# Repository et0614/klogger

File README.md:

# K-Logger v3 — 扉開閉記録装置

VL53L1X ToF距離センサで扉の開閉を検出し、内蔵フラッシュメモリに記録するデータロガー。
v2 からの主な変更点は以下のとおり（開発中）。

| 項目 | v2 | v3 |
|---|---|---|
| MCU | AVR32DB32 | AVR64DU32（ネイティブUSB） |
| PC通信 | CP2102N（USB-UART、要ドライバ） | USB-CDC（ドライバ不要） |
| 記録媒体 | microSD（FatFs、CSV） | W25Q128 16MB（バイナリ、PCツールでCSV化） |
| 電源 | 単3×1 | 単4×1、USB接続中はUSB給電（自動切替） |
| USB端子 | micro-B | Type-C |
| 電源スイッチ | スライド | なし（ボタン長押しでソフトOFF） |
| 基板CAD | Eagle | Fusion |

旧版（v2）は [v2/](v2/README.md) を参照。

## ディレクトリ構成

```
docs/
  index.html            ブラウザ版の操作ページ（GitHub Pages）
  images/               基板・3D外観画像
hardware/
  BOM.xlsx              設計用部品表（JLCPCB部品番号・リンク付き）
  datasheets/           主要部品データシート（ファイル名=参照記号）
  pcb/                  Fusion設計データ(klogger.f3z)、回路図PDF
  fab/                  JLCPCB入稿データ（ガーバー、JLCPCB_BOM.xlsx、JLCPCB_CPL.xlsx）
firmware/klogger.X/     MPLAB X プロジェクト（AVR64DU32, MCC Melody: klogger.mc3）。アプリは 0x0A00 以降に置く
firmware/bootloader/    USB ブートローダ（euboot）。USB でのファームウェア更新と、量産用の1ファイル化 (build_production_hex.py)
software/python/        PCツール: klogger_gui.py（GUI）、klogger.py（コマンド版・通信ライブラリ）、build_exe.bat（exe化）
v2/                     旧版 K-Logger v2 一式（凍結）
```

## バージョン

- 製品世代: K-Logger v3（v2 の後継）
- 基板: 3.1（シルク表記「Version 3.1」。3.0 からはシルクのみ変更、履歴は `hardware/fab/README.md`）。修正ごとに 3.2, 3.3 … と上げる。リポジトリには最新版のみを置き、過去の版は Git の履歴で参照する
- ファームウェア: 現在 3.2.0（`hello` 応答の `fw`。`firmware/klogger.X/version.h`）

## 使い方

### 動作モード
| 状態 | 入り方 | 動作 | LED |
|---|---|---|---|
| USB通信 | USBを挿す | PCツールからの操作を受け付ける（USB給電） | 1秒ごとに2回点滅 |
| 記録 | PCツールで記録開始 | 記録間隔ごとに距離を記録。USBを抜いても続ける | 消灯 |
| 待機（ソフトOFF） | USB無しで電池を入れる / 記録中にボタン5秒長押し / 電池切れ | 何もしない（省電力） | 消灯 |

- ボタンを押している間はLEDが点灯する（生存確認）。5秒長押しでリセット（記録中なら記録停止）。
- 記録中にUSBを挿すと記録を止めてUSB通信モードに戻る（データは保存される）。
- 記録開始時に既存データは消去される。先に読み出しておくこと。
- 電池を抜くと、まだフラッシュに書いていない最大128件（1秒間隔で約2分）が失われる。

### 消費電流・電池寿命
記録間隔1秒・測距条件 short / 20ms / ROI 4x4（既定、FW 3.1.1 から）で、記録中の電流は電池側で平均約0.6mA（実測、2026-11-20）。内訳は測距が約0.4mA、測距の合間（マイコンのスリープ、距離センサの待機、昇圧ICなど）が約0.2mA。タイミングバジェット 50ms では平均約1.2mA（測距が約0.9mA）で、Eneloop Pro（単4、約930mAh）を満充電して設置した実績は約16日だった（計算上は約1か月。電池電圧が下がるほど電池側の電流は増える）。
測距の分は記録間隔とタイミングバジェットにほぼ比例して減る。20ms は VL53L1X の最小値（short のみ）。50ms に比べて距離のばらつきは約2倍（近距離の標準偏差 約1mm → 約2mm）になり、遠い対象や強い外光では失敗が増えるが、扉の開閉の検出には影響しない。
待機中（記録停止後）も約0.2mA 流れる（昇圧IC の自己消費 17µA が主。3.3V を保つ限り減らせない）。満充電でも約半年で空になるので、使わないときは電池を抜く。
電流はクランプ電流計で、配線を5回巻いて測った（1回巻きでは1mA以下の精度が足りず、以前の「約0.5mA」は過小だった）。測距は1秒に1回の短いパルスなので、1秒ごとの読み取り値は、測距のパルスを含むかどうかで2つの値を行き来する（20ms で約0.2mA と約0.9mA）。平均はその読み取り値の平均で見る。

### ブラウザ版
パソコンの Chrome または Edge で https://et0614.github.io/klogger/ を開き、USB でつないで「接続」を押す（インストール不要）。記録の開始、CSV の保存（日ごとの v2 形式も可）、データの消去、ライブ表示、距離の校正、測距条件、自己診断ができる。ページは `docs/index.html`（Web Serial で USB の仮想 COM ポートを開く。GitHub Pages で main ブランチの `/docs` を公開する）。手元で試すときは `docs` で `python -m http.server` を実行して http://localhost:8000/ を開く（Web Serial は https か localhost でしか動かない）。

### PCツール（GUI）
[Releases](https://github.com/et0614/klogger/releases) から `KLogger.exe` をダウンロードしてダブルクリックで起動する（Pythonは不要）。
署名の無いexeのため、初回に Windows SmartScreen が出たら「詳細情報」→「実行」を選ぶ。
Pythonがある場合は `pip install pyserial` の後に `python klogger_gui.py` でも起動できる。画面表示は英語。

1. USBを挿して **Connect**（ポートは自動検出）。上部に機器情報（FW、機体ID、電池電圧、保存件数、記録期間、測距条件）が出る。
2. **Logging** タブ: 記録間隔を入れて **Start logging**。時刻はPCに合わせられ、既存データは消去される。開始すると機器はUSBから切り離されるので、そのまま抜いて設置する。
3. 回収したらUSBを挿して（記録は自動で止まる）**Connect**。**Data** タブの **Save as CSV** で保存する（v2互換の日別CSVも選べる）。
4. **Live view** タブ: 距離をリアルタイム表示（設置位置の確認用）。
5. **Settings** タブ: 測距モード（Short/Long）、タイミングバジェット、ROI、自己診断。

### 距離校正（GUIの Calibration タブ）
距離のオフセット（測定値のずれ）を補正する。結果は機器に保存される。

1. 先に **Settings** タブで、実際に使う測距条件にしておく（条件を変えたら校正し直す）。
2. グレーの反射板（反射率17%前後。写真用18%グレーカードなど、10cm角以上）をセンサ正面に垂直に置く。距離は140mmを推奨。直射日光は避ける。
3. 目標距離（Target distance）を入力し **Start live reading**。直近20回の平均・ばらつき（SD）・目標との差が表示される。
4. ランプが緑（全数が有効かつ SD 3mm 以下）になったら **Calibrate**。50回測定して オフセット = 目標距離 − 平均 を保存する。
5. 校正後は補正済みの距離が表示されるので、反射板を別の距離に動かしてずれを確認する。結果が悪ければ **Restore previous offset**（元に戻す）や **Reset offset to 0** を使う。

### PCツール（コマンド版 `software/python/klogger.py`）
`pip install pyserial` の後、USBを挿して実行する（COMポートは自動検出）。

```
python klogger.py info              機器情報・状態・電池電圧
python klogger.py start -i 1        時刻合わせ＋記録開始（記録間隔1秒）
python klogger.py read              保存データをCSVに保存（--daily フォルダ でv2互換の日別CSV）
python klogger.py measure           距離を連続表示（保存しない）
python klogger.py calibrate 140     オフセット校正（対象物を140mmに置く）
python klogger.py tof --mode long --tb 33 --roi 8   測距条件の変更（--offset でオフセットを直接設定）
python klogger.py selftest          自己診断
python klogger.py clear             保存データの消去
python klogger.py update xxx.hex    USB でファームウェアを更新（ブートローダで起動しておく）
```

exeの作り方: `pip install pyinstaller` の後に `build_exe.bat` を実行すると `dist\KLogger.exe` ができる。`software/python/` に `avrdude.exe` と `avrdude.conf`（avrdude 8.0 以降）を置いておくと exe に同梱され、Firmware タブでファームウェアを更新できる。

### ファームウェアの更新（FW 3.2.0 以降）
フラッシュの先頭 2.5 KB に USB ブートローダ（euboot）を置き、ファームウェアは `0x0A00` 以降に置く。電池と USB を外し、ボタンを押したまま USB をつなぐとブートローダに入る（LED がブートローダの点滅になったら離す）。PCツールの Firmware タブ（または `klogger.py update`、`avrdude`）で書き換える。3.1.x 以前（ブートローダなし）の機体は、初回だけ PICkit で `firmware/bootloader/hex/klogger_combined.hex` を書き込む。詳細は [firmware/bootloader/README.md](firmware/bootloader/README.md)。

### 記録データ形式
1レコード2バイト（W25Q128に連続保存、16MBで約838万件＝1秒間隔で約97日）。
bit15–13が状態コード（0=有効, 1=sigma fail, 2=signal fail, 3=out of bounds, 4=wraparound, 5=min range, 6=その他）、
bit12–0が距離[mm]。0xFFFEは計測失敗。時刻は 記録開始時刻 + index × 記録間隔 で復元する。

## 開発メモ
- USB: AVR64DU のエラッタ 2.8.1（マルチパケットOUT転送は偶数アドレス必須）により、MCC生成の `usbCDCLineCoding` が奇数アドレスに置かれるとPCでCOMポートが開けなくなる。`usb_comm.c` で偶数アドレスのバッファを使って回避している。MCCで再生成しても消えない。
- センサの GPIO1（10kプルアップ、アクティブLow）は測定完了の立ち下がり割り込み（PA1）ですぐ読み取って解除する。放置するとプルアップに電流が流れ続ける。

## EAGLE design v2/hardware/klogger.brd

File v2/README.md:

# K-Logger v2 — 扉開閉記録装置（旧版・凍結）

> このディレクトリは K-Logger v2（AVR32DB32 + microSD + CP2102N、単3電池）の一式であり、今後は更新しない。
> 最新版は [リポジトリ直下の README](../README.md)（K-Logger v3）を参照。整理前の状態はタグ `v2-final` で参照できる。

VL53L1X ToF距離センサで扉の開閉を検出し、タイムスタンプ付きで microSD に記録するデータロガー。
詳細仕様は「[扉開閉記録装置K-Logger_説明書.pdf](扉開閉記録装置K-Logger_説明書.pdf)」を参照。

## ディレクトリ構成

```
firmware/klogger.X/   MPLAB X プロジェクト（ファームウェア）
hardware/             回路図・基板 (Eagle)、BOM、ガーバー
software/             PC側操作ツール
  windows-console/    PowerShell + バッチファイル版
  python/             Python 版 (クロスプラットフォーム)
```

## ファームウェア開発環境

| 項目 | 内容 |
|---|---|
| MCU | AVR32DB32 (Flash 32KB / RAM 4KB / EEPROM 512B, F_CPU = 4MHz) |
| IDE | MPLAB X IDE v6.30 + MCC Melody (設定ファイル: `klogger.mc3`) |
| コンパイラ | XC8 v3.10 (Free ライセンス, -O2 + リンカ `-mrelax`) |
| DFP | AVR-Dx_DFP 2.7.321 |
| 書き込み | UPDI (PICkit 等) |

ビルドは MPLAB X でプロジェクト `firmware/klogger.X` を開いて Clean and Build。
Flash 使用量が上限 32KB の約 90% のため、機能追加時はサイズに注意。

### 主要ペリフェラル

- USART0 (PA0/PA1): 9600 bps 8N1 — PC との通信
- TWI1 (PF2/PF3): VL53L1X 距離センサ (XSHUT=PD3, INT=PD4)
- SPI1 (PC0–PC2, CS=PC3): microSD (FatFs + ChaN MMC ドライバ)
- RTC: 外部 32.768kHz クリスタル、PIT 1 秒周期で時刻管理
- ADC0 (AIN5=PD5): 電源電圧監視
- PD2: 状態表示 LED

## UART コマンド

起動後 60 秒間（コマンド受信ごとに延長）だけ UART 待機する。9600 bps 8N1、行末 CR+LF。

| コマンド | 応答 | 説明 |
|---|---|---|
| `ID?` | `K-Logger v2.2` | 機器識別 |
| `SETTIME yyyy-mm-ddTHH:MM:SS` | `Time set OK` | 時計設定 |
| `CALIBRATE <mm>` | `CAL OK, offset:<n>` | 距離校正 (10–500 mm) |
| `CMEASURE` | `Start continuous measuring` 後、`MES <mm>` を連続送出 | 連続測定開始 |
| `STOP` | `Stop continuous measuring` | 連続測定停止 |

## PC 側ツール

USB-シリアル変換は CP210x (`software/CP210x_Universal_Windows_Driver.zip`)。

- **Windows**: `software/windows-console/` の `SetTime.bat` / `Calibrate.bat` / `Measure.bat`
- **Python**: `software/python/` の `klogger_tool.py`（要 pyserial、使い方は同フォルダの README 参照）

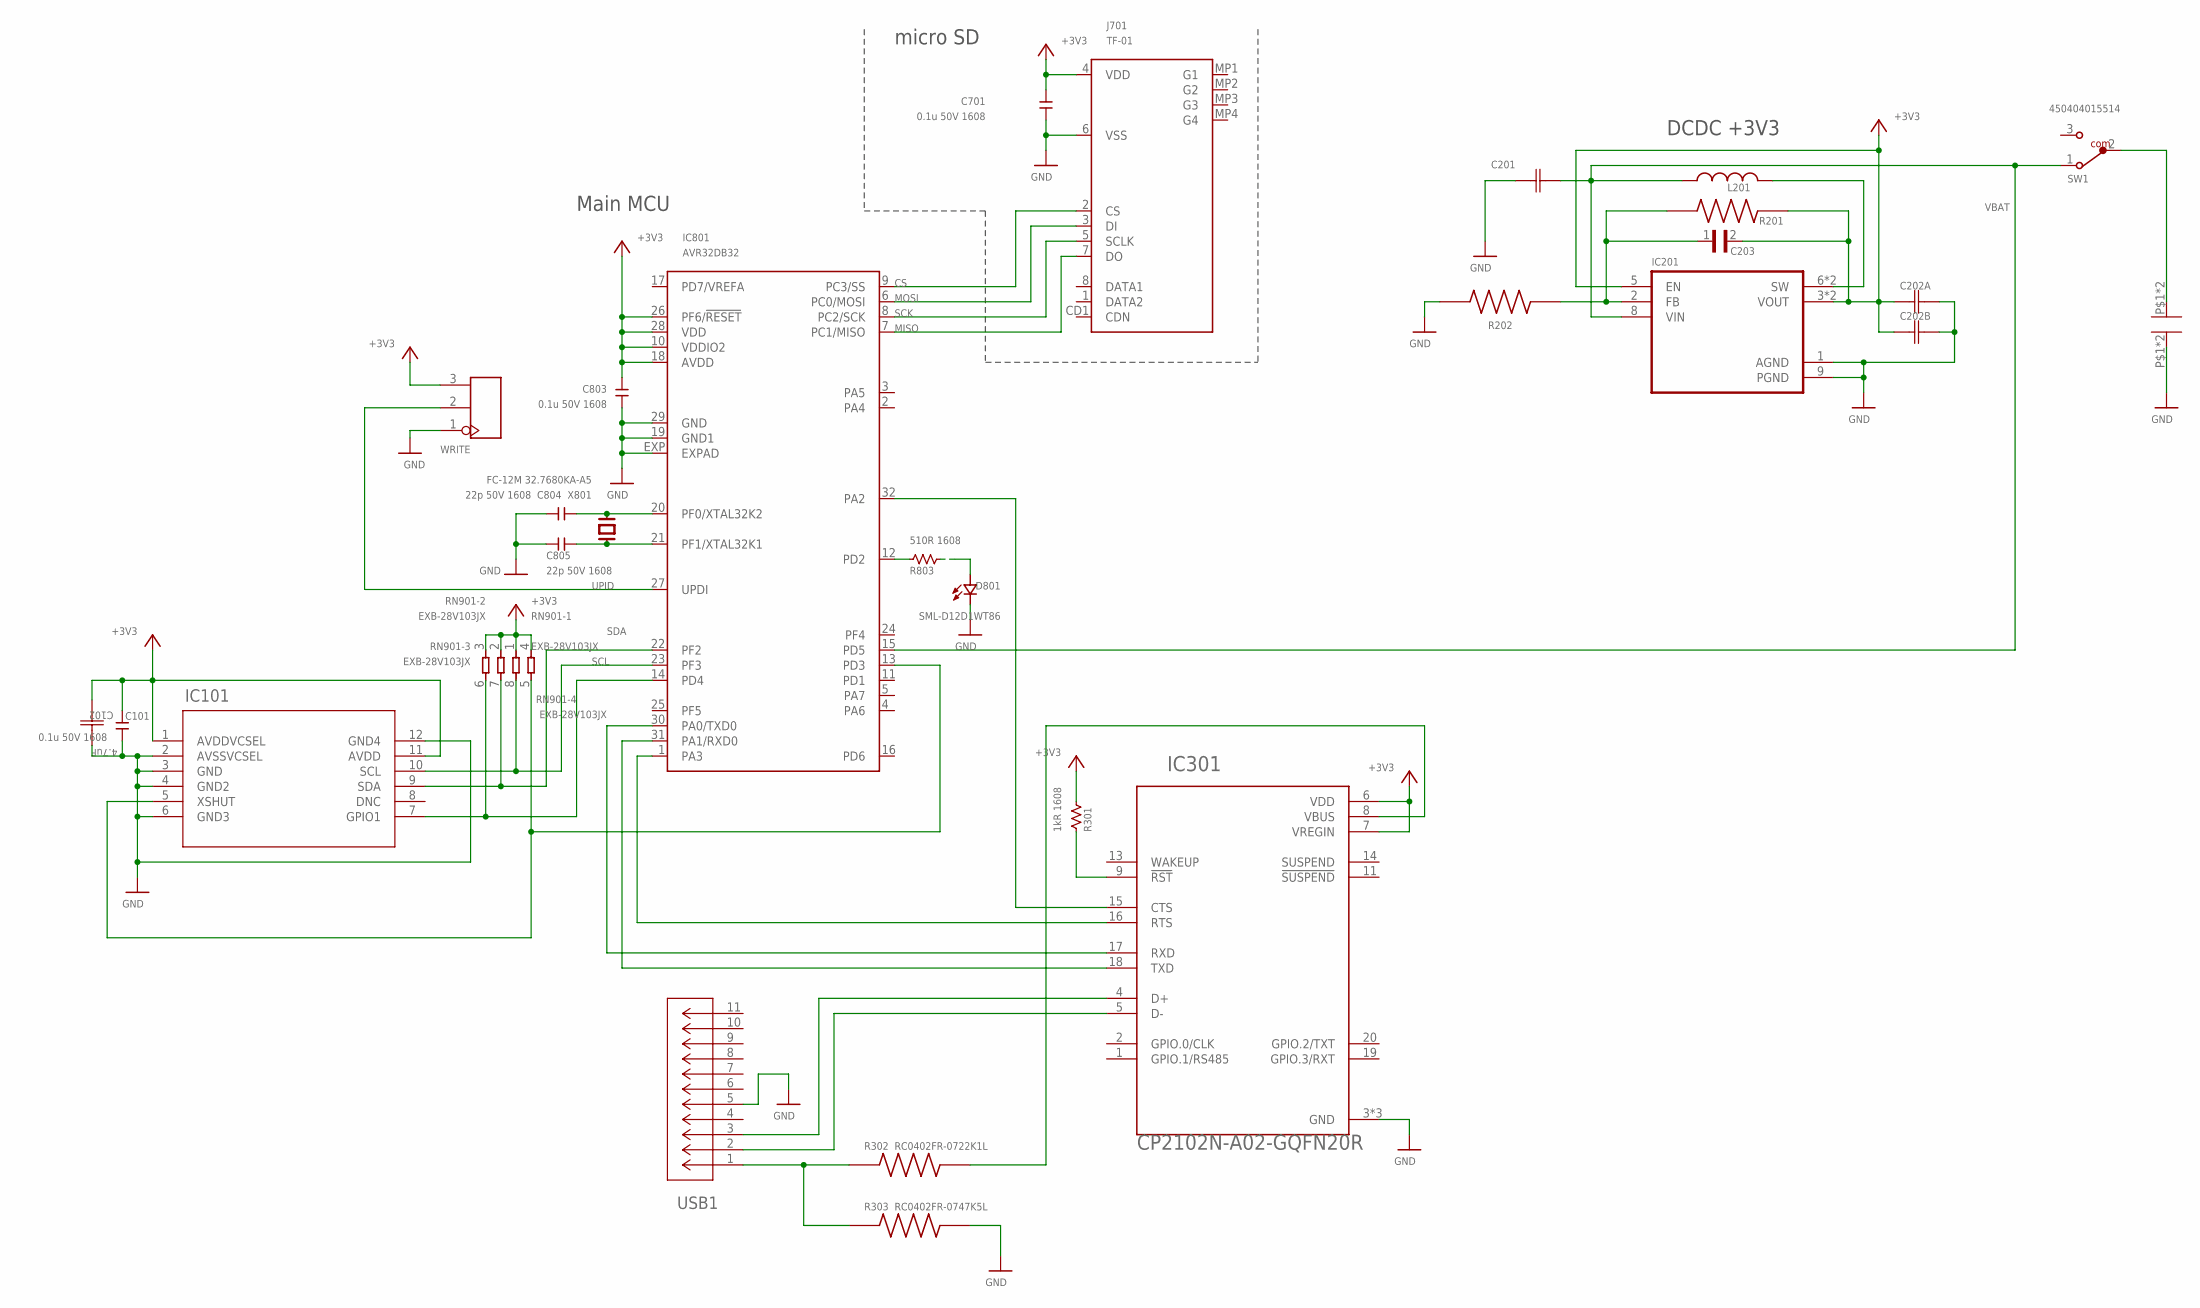
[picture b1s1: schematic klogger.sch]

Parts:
BATM: 53
BATP: 53
C101, C701, C803: 0.1u 50V 1608; C-1608/0603
C102: 4.7uF; CAPC2013X135N
C201: GRM155R61A106ME11DCAP_GRM155R61A106ME11_MUR; CAP_GRM155R61A106ME11_MUR
C202A, C202B: GRM188R61A226ME15DCAP_GRM18ME15D_1P6XP8_MUR; CAP_GRM18ME15D_1P6XP8_MUR
C203: GJM1555C1H4R7CB01D; CAPC1005X55N
C804, C805: 22p 50V 1608; C-1608/0603
D801: SML-D12D1WT86; SMD-1608
IC101: VL53L0CXV0DH/1LGA12_STM; LGA12_STM
IC201: TPS61021ADSGR; SON50P200X200X80-9N
IC301: CP2102N-A02-GQFN20R; SILABS_CP2102N-A02-GQFN20R
IC801: AVR32DB32; HVQFN32
J701: TF-01; TF-01A
L201: DFE252012PD-R47M=P2; INDC2520X120N
R201: RC0402FR-071M24L; RESC1005X40N
R202: RC0402FR-07390KL; RESC1005X40N
R301: 1kR 1608; R-1608/0603
R302: RC0402FR-0722K1L; RESC1005X40N
R303: RC0402FR-0747K5L; RESC1005X40N
R803: 510R 1608; R-1608/0603
RN901: EXB-28V103JX; RESCAXS50P200X100X45-8N
SW1: 450404015514
USB1: 1050170001CONN_1050170001_MOL; CONN_1050170001_MOL
WRITE: 3p-2.54; H3-2.54
X801: FC-12M 32.7680KA-A5; X2-SMD-L2.0X1.2X0.55MM

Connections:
+3V3: C101.P$1 (1), C102.2 (C2), C202A.1, C202B.1, C203.2, C701.P$1 (1), C803.P$1 (1), IC101.1 (AVDDVCSEL), IC101.11 (AVDD), IC201.3 (VOUT), IC201.4 (VOUT), IC201.5 (EN), IC301.6 (VDD), IC301.7 (VREGIN), IC801.10 (VDDIO2), IC801.18 (AVDD), IC801.26 (PF6/!RESET), IC801.28 (VDD), J701.4 (VDD), R201.2, R301.2, RN901.1, RN901.2 (1), RN901.3 (1), RN901.4 (1), WRITE.3
CS: IC801.9 (PC3/SS), J701.2 (CS)
FB: C203.1, IC201.2 (FB), R201.1, R202.2
GND: BATM.P$1, BATM.P$2, C101.P$2 (2), C102.1 (C1), C201.1, C202A.2, C202B.2, C701.P$2 (2), C803.P$2 (2), C804.P$2 (2), C805.P$2 (2), D801.2 (C), IC101.2 (AVSSVCSEL), IC101.3 (GND), IC101.4 (GND2), IC101.6 (GND3), IC101.12 (GND4), IC201.1 (AGND), IC201.9 (PGND), IC301.3 (GND), IC301.12 (GND), IC301.21 (GND), IC801.19 (GND1), IC801.29 (GND), IC801.EXP (EXPAD), J701.6 (VSS), R202.1, R303.2, USB1.5, WRITE.1
GPIO: IC101.7 (GPIO1), IC801.14 (PD4), RN901.6 (2)
LED: IC801.12 (PD2), R803.1
MCTS: IC301.16 (RTS), IC801.1 (PA3)
MISO: IC801.7 (PC1/MISO), J701.7 (DO)
MOSI: IC801.6 (PC0/MOSI), J701.3 (DI)
MRTS: IC301.15 (CTS), IC801.32 (PA2)
MRX: IC301.18 (TXD), IC801.31 (PA1/RXD0)
MTX: IC301.17 (RXD), IC801.30 (PA0/TXD0)
unnamed: BATP.P$1, BATP.P$2, SW1.2
unnamed: R302.1, R303.1, USB1.1
unnamed: IC301.9 (!RST), R301.1
unnamed: IC301.8 (VBUS), R302.2
unnamed: D801.1 (A), R803.2
unnamed: C804.P$1 (1), IC801.20 (PF0/XTAL32K2), X801.1
unnamed: C805.P$1 (1), IC801.21 (PF1/XTAL32K1), X801.2
SCK: IC801.8 (PC2/SCK), J701.5 (SCLK)
SCL: IC101.10 (SCL), IC801.23 (PF3), RN901.8 (2)
SDA: IC101.9 (SDA), IC801.22 (PF2), RN901.7 (2)
SW: IC201.6 (SW), IC201.7 (SW), L201.2
UPID: IC801.27 (UPDI), WRITE.2
USBDM: IC301.5 (D-), USB1.2
USBDP: IC301.4 (D+), USB1.3
VBAT: C201.2, IC201.8 (VIN), IC801.15 (PD5), L201.1, SW1.1
XSHUT: IC101.5 (XSHUT), IC801.13 (PD3), RN901.5 (2)

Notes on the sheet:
Main MCU
DCDC +3V3
micro SD

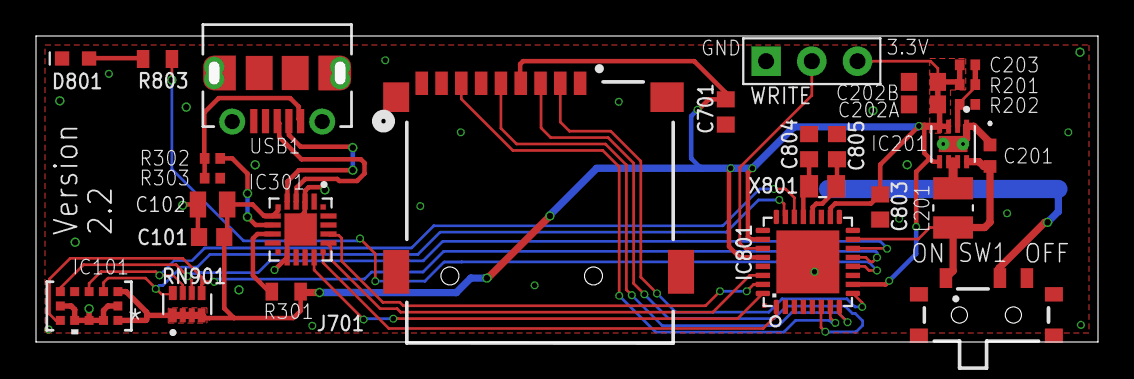
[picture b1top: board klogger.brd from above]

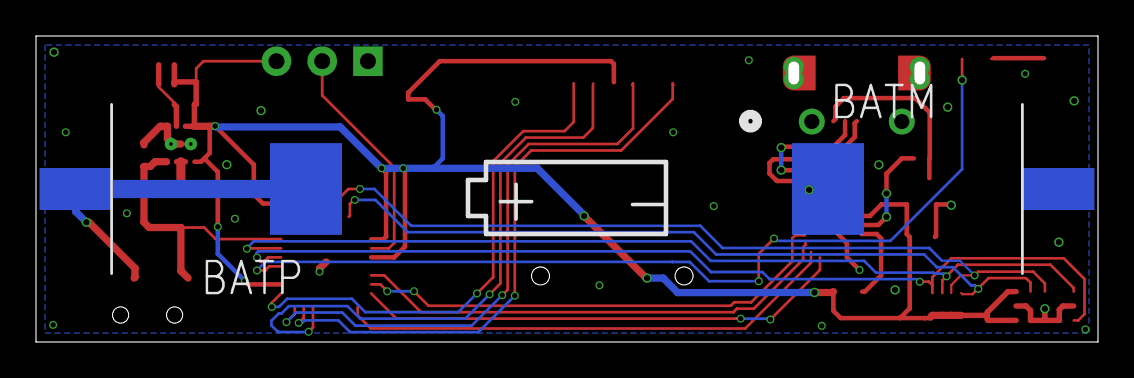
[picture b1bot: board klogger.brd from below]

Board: 2 copper layers, 59.0 x 17.0 mm, 30 parts (2 on the bottom side), 28 nets.

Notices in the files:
parts and their libraries:
COPYRIGHT: Copyright (C) 2025 Ultra Librarian. All rights reserved.
